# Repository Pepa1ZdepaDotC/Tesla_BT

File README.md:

# Tesla 1128A repair and BT upgrade

[Schematic](https://github.com/Pepa1ZdepaDotC/Tesla_BT/blob/main/Tesla_rev_2/Tesla_sextant_BT.pdf)

[Interactive BOM](https://htmlpreview.github.io/?https://github.com/Pepa1ZdepaDotC/Tesla_a.s._BT/blob/main/BOM/ibom.html)

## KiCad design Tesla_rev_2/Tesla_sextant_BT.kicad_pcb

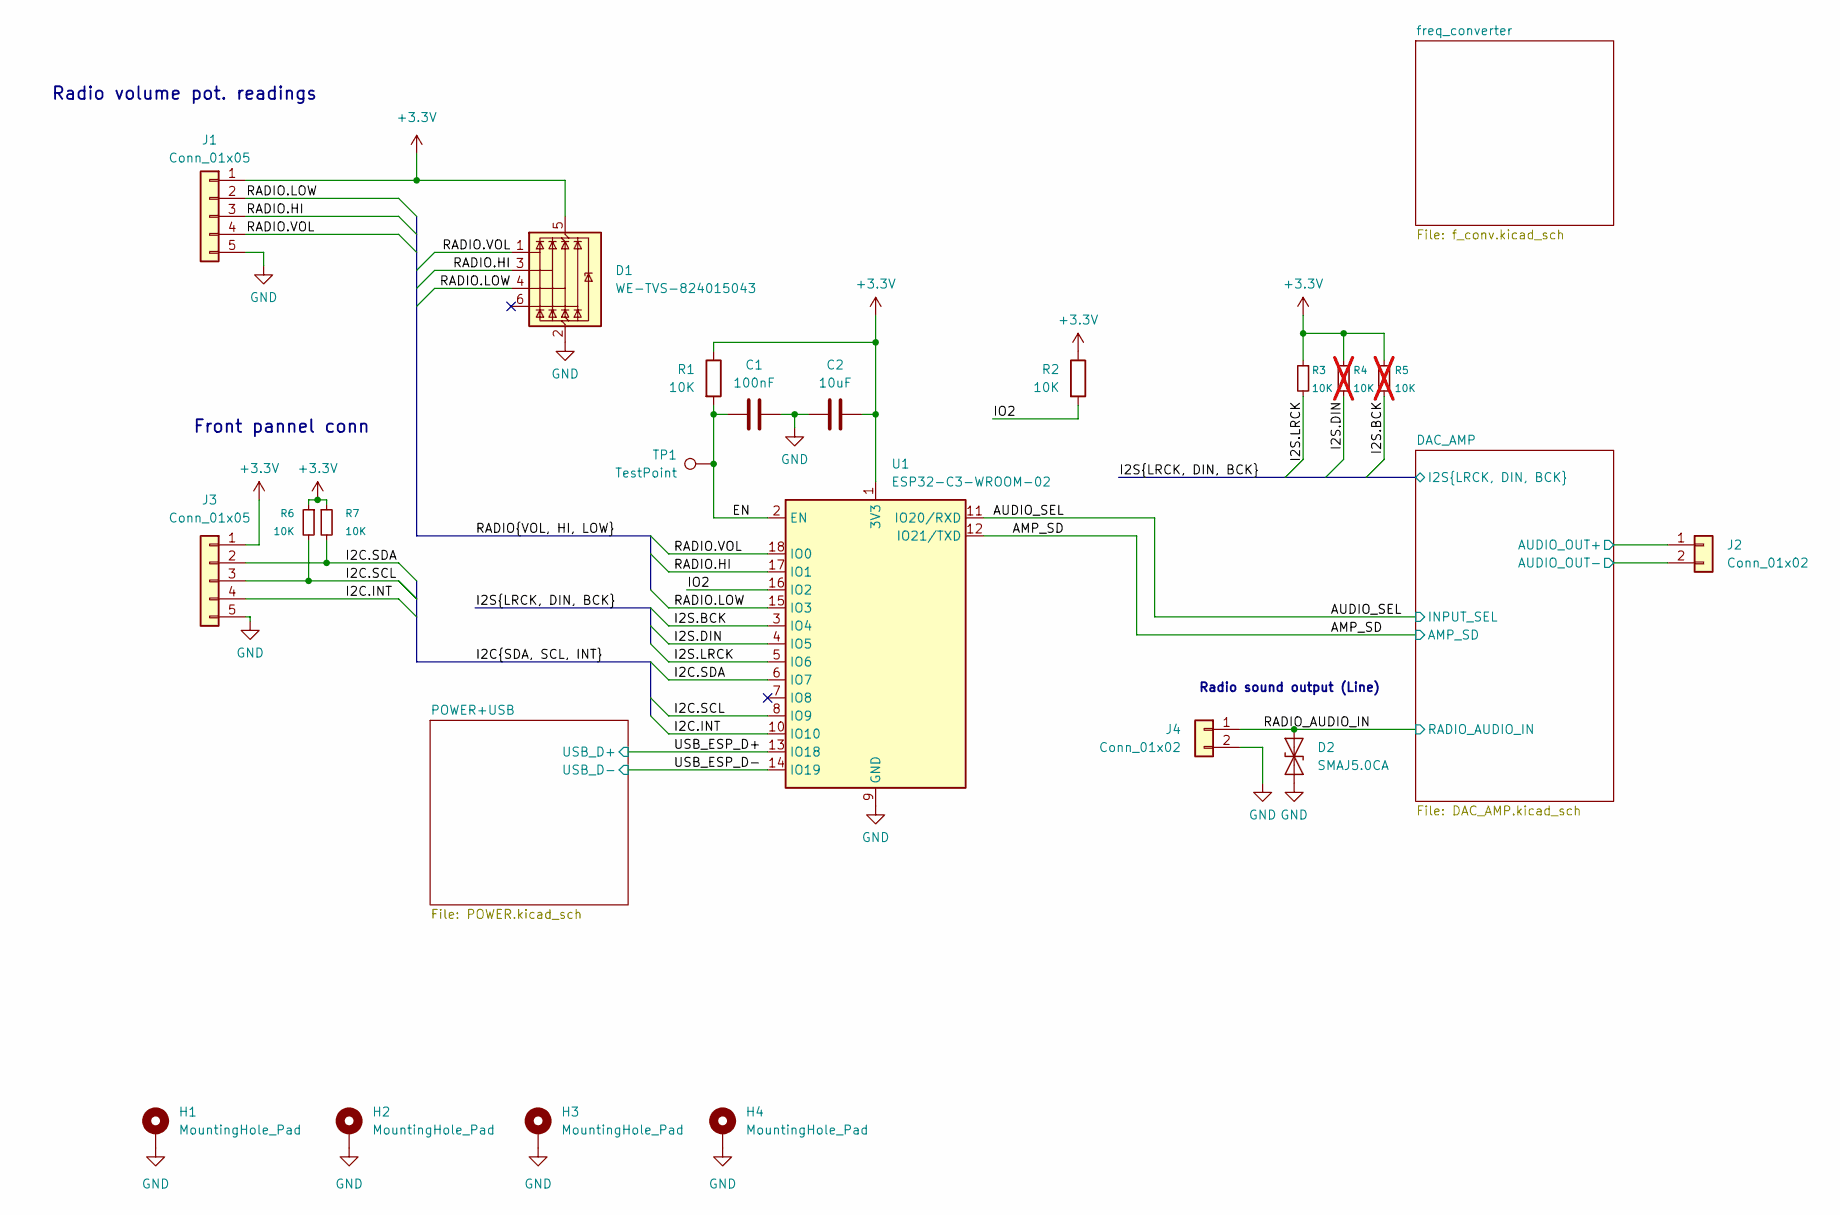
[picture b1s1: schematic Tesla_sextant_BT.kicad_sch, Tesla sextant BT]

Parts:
C1: 100nF; C_0805_2012Metric
C2: 10uF; C_0805_2012Metric
D1: WE-TVS-824015043; SOT-23-6
D2: SMAJ5.0CA; D_SMA
H1, H2, H3, H4: MountingHole_Pad; MountingHole_4.3mm_M4_DIN965_Pad_TopBottom
J1, J3: Conn_01x05; PinSocket_1x05_P2.00mm_Vertical
J2, J4: Conn_01x02; Conn_Solder_1x02_SMD
R1, R2, R3, R6, R7: 10K; R_0805_2012Metric
R4, R5: 10K; R_0805_2012Metric; not fitted
TP1: TestPoint; TestPoint_Pad_D2.5mm
U1: ESP32-C3-WROOM-02

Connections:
+3.3V: C2.1, D1.5 (VBUS), J1.1, J3.1, R1.1, R2.1, R3.1, R4.1, R5.1, R6.1, R7.1, U1.1 (3V3); also elsewhere on the board
/AMP_SD: U1.12 (IO21/TXD); also elsewhere on the board
/AUDIO_SEL: U1.11 (IO20/RXD); also elsewhere on the board
/DAC_AMP/AUDIO_OUT+: J2.1; also elsewhere on the board
/DAC_AMP/AUDIO_OUT-: J2.2; also elsewhere on the board
/EN: C1.2, R1.2, TP1.1, U1.2 (EN)
/I2C.INT: J3.4, U1.10 (IO10)
/I2C.SCL: J3.3, R6.2, U1.8 (IO9)
/I2C.SDA: J3.2, R7.2, U1.6 (IO7)
/I2S.BCK: R5.2, U1.3 (IO4); also elsewhere on the board
/I2S.DIN: R4.2, U1.4 (IO5); also elsewhere on the board
/I2S.LRCK: R3.2, U1.5 (IO6); also elsewhere on the board
/IO2: R2.2, U1.16 (IO2)
/RADIO.HI: D1.3 (I/O2), J1.3, U1.17 (IO1)
/RADIO.LOW: D1.4 (I/O3), J1.2, U1.15 (IO3)
/RADIO.VOL: D1.1 (I/O1), J1.4, U1.18 (IO0)
/RADIO_AUDIO_IN: D2.1 (A1), J4.1; also elsewhere on the board
/USB_ESP_D+: U1.13 (IO18); also elsewhere on the board
/USB_ESP_D-: U1.14 (IO19); also elsewhere on the board
GND: C1.1, C2.2, D1.2 (GND), D2.2 (A2), H1.1, H2.1, H3.1, H4.1, J1.5, J3.5, J4.2, U1.9 (GND), U1.19 (GND); also elsewhere on the board

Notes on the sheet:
Radio volume pot. readings
Radio sound output (Line)
Front pannel conn

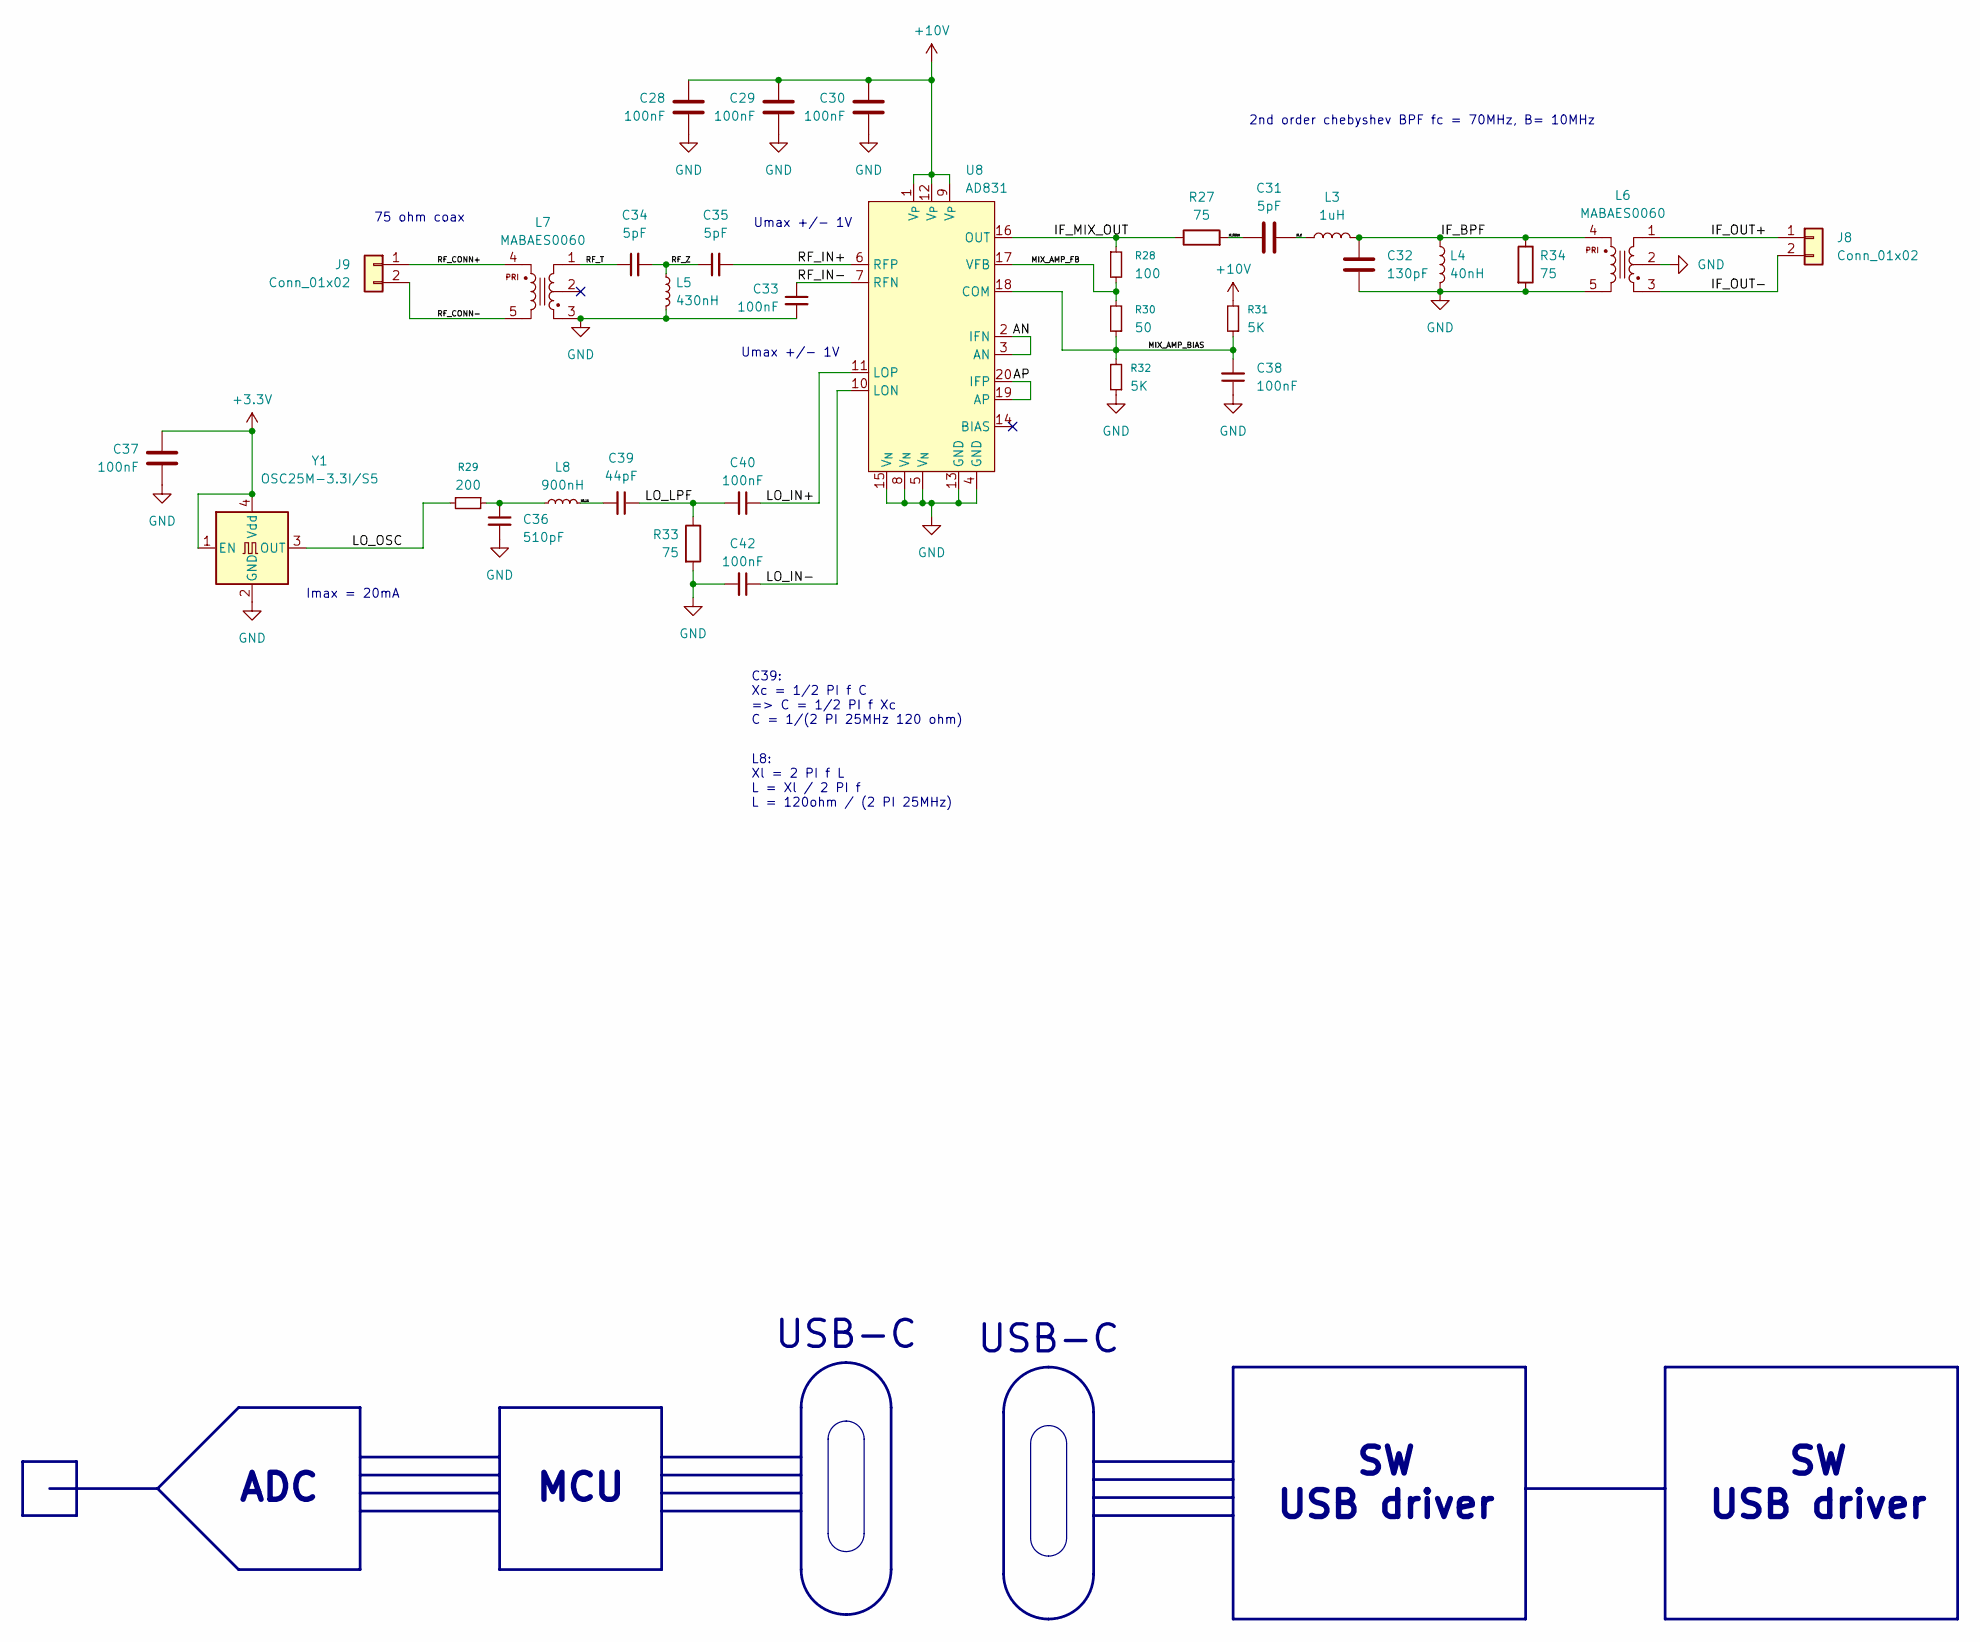
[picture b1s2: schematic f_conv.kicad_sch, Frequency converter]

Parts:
C28, C29, C30, C37, C38: 100nF; C_0805_2012Metric
C31, C34, C35: 5pF; C_0603_1608Metric
C32: 130pF; C_0603_1608Metric
C33, C40, C42: 100nF; C_0603_1608Metric
C36: 510pF; C_0603_1608Metric
C39: 44pF; C_0603_1608Metric
J8, J9: Conn_01x02; Conn_Solder_1x02_SMD
L3: 1uH; L_0603_1608Metric
L4: 40nH; L_0603_1608Metric
L5: 430nH; L_0603_1608Metric
L6, L7: MABAES0060; SM-22
L8: 900nH; L_0603_1608Metric
R27, R33, R34: 75; R_0805_2012Metric
R28: 100; R_0805_2012Metric
R29: 200; R_0805_2012Metric
R30: 50; R_0805_2012Metric
R31, R32: 5K; R_0805_2012Metric
U8: AD831; PLCC-20
Y1: OSC25M-3.3I/S5; Oscillator_SMD_Fordahl_DFAS15-4Pin_5.0x3.2mm_HandSoldering

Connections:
+3.3V: C37.2, Y1.1 (EN), Y1.4 (Vdd); also elsewhere on the board
+10V: C28.2, C29.2, C30.2, R31.2, U8.1 (V_{P}), U8.9 (V_{P}), U8.12 (V_{P}); also elsewhere on the board
/freq_converter/AN: U8.2 (IFN), U8.3 (AN)
/freq_converter/AP: U8.19 (AP), U8.20 (IFP)
/freq_converter/IF_BPF: C32.2, L3.2, L4.1, L6.4, R34.1
/freq_converter/IF_C: C31.2, L3.1
/freq_converter/IF_MIX_OUT: R27.1, R28.1, U8.16 (OUT)
/freq_converter/IF_OUT+: J8.1, L6.1
/freq_converter/IF_OUT-: J8.2, L6.3
/freq_converter/IF_TERM: C31.1, R27.2
/freq_converter/LO_IN+: C40.1, U8.11 (LOP)
/freq_converter/LO_IN-: C42.1, U8.10 (LON)
/freq_converter/LO_L1: C39.2, L8.2
/freq_converter/LO_LPF: C39.1, C40.2, R33.1
/freq_converter/LO_OSC: R29.2, Y1.3 (OUT)
/freq_converter/MIX_AMP_BIAS: C38.2, R30.1, R31.1, R32.2, U8.18 (COM)
/freq_converter/MIX_AMP_FB: R28.2, R30.2, U8.17 (VFB)
/freq_converter/RF_CONN+: J9.1, L7.4
/freq_converter/RF_CONN-: J9.2, L7.5
/freq_converter/RF_IN+: C35.2, U8.6 (RFP)
/freq_converter/RF_IN-: C33.1, U8.7 (RFN)
/freq_converter/RF_T: C34.1, L7.1
/freq_converter/RF_Z: C34.2, C35.1, L5.1
GND: C28.1, C29.1, C30.1, C32.1, C33.2, C36.2, C37.1, C38.1, C42.2, L4.2, L5.2, L6.2, L6.5, L7.3, R32.1, R33.2, R34.2, U8.4 (GND), U8.5 (V_{N}), U8.8 (V_{N}), U8.13 (GND), U8.15 (V_{N}), Y1.2 (GND); also elsewhere on the board
unnamed: C36.1, L8.1, R29.1

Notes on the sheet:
L8: Xl = 2 PI f L L = Xl / 2 PI f L = 120ohm / (2 PI 25MHz)
2nd order chebyshev BPF fc = 70MHz, B= 10MHz
Umax +/- 1V
SW USB driver
ADC
C39: Xc = 1/2 PI f C => C = 1/2 PI f Xc C = 1/(2 PI 25MHz 120 ohm)
Imax = 20mA
USB-C
75 ohm coax
MCU

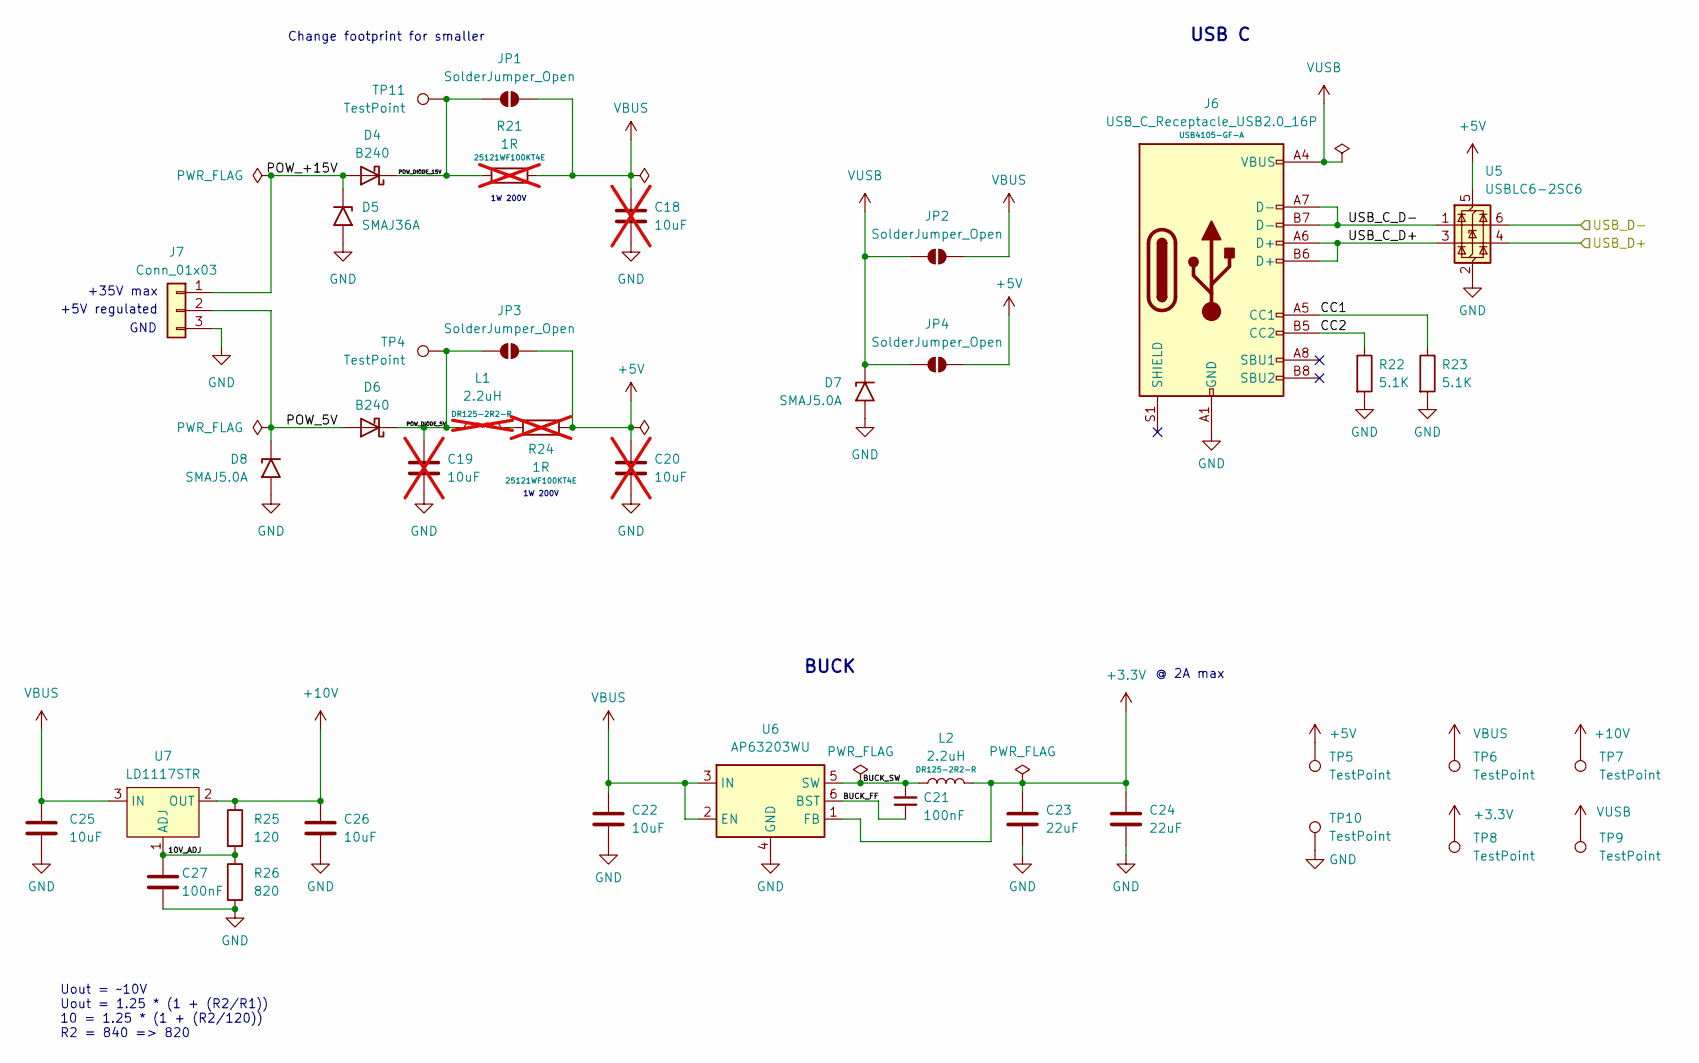
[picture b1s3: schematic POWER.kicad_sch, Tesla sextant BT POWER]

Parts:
C18, C19, C20: 10uF; C_0805_2012Metric; not fitted
C21, C27: 100nF; C_0805_2012Metric
C22, C25, C26: 10uF; C_0805_2012Metric
C23, C24: 22uF; C_0805_2012Metric
D4, D6: B240; D_SMB
D5: SMAJ36A; D_SMA
D7, D8: SMAJ5.0A; D_SMA
J6: USB_C_Receptacle_USB2.0_16P; USB_C_Receptacle_GCT_USB4105-xx-A_16P_TopMnt_Horizontal; Part_num USB4105-GF-A
J7: Conn_01x03; Conn_Solder_1x03_SMD
JP1, JP2, JP3, JP4: SolderJumper_Open; SolderJumper-2_P1.3mm_Open_TrianglePad1.0x1.5mm
L1: 2.2uH; L_12x12mm_H8mm; Part_num DR125-2R2-R; not fitted
L2: 2.2uH; L_12x12mm_H8mm; Part_num DR125-2R2-R
R21, R24: 1R; R_2512_6332Metric; Part_num 25121WF100KT4E; not fitted
R22, R23: 5.1K; R_0805_2012Metric
R25: 120; R_0805_2012Metric
R26: 820; R_0805_2012Metric
TP4, TP5, TP6, TP7, TP8, TP9, TP10, TP11: TestPoint; TestPoint_Pad_D2.5mm
U5: USBLC6-2SC6; SOT-23-6
U6: AP63203WU; TSOT-23-6
U7: LD1117STR; SOT-223

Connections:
+3.3V: C23.1, C24.1, L2.2, TP8.1, U6.1 (FB); also elsewhere on the board
+5V: C20.1, JP3.2 (B), JP4.2 (B), R24.1, TP5.1, U5.5 (VBUS); also elsewhere on the board
+10V: C26.1, R25.1, TP7.1, U7.2 (OUT), U7.4 (OUT); also elsewhere on the board
/POWER+USB/10V_ADJ: C27.1, R25.2, R26.1, U7.1 (ADJ)
/POWER+USB/BUCK_FF: C21.1, U6.6 (BST)
/POWER+USB/BUCK_SW: C21.2, L2.1, U6.5 (SW)
/POWER+USB/CC1: J6.A5 (CC1), R23.1
/POWER+USB/CC2: J6.B5 (CC2), R22.1
/POWER+USB/POW_5V: D6.2 (A), D8.1 (A1), J7.2
/POWER+USB/POW_+15V: D4.2 (A), D5.1 (A1), J7.1
/POWER+USB/POW_DIODE_5V: C19.1, D6.1 (K), JP3.1 (A), L1.1, TP4.1
/POWER+USB/POW_DIODE_15V: D4.1 (K), JP1.1 (A), R21.2, TP11.1
/POWER+USB/USB_C_D+: J6.A6 (D+), J6.B6 (D+), U5.3 (I/O2)
/POWER+USB/USB_C_D-: J6.A7 (D-), J6.B7 (D-), U5.1 (I/O1)
/USB_ESP_D+: U5.4 (I/O2); also elsewhere on the board
/USB_ESP_D-: U5.6 (I/O1); also elsewhere on the board
GND: C18.2, C19.2, C20.2, C22.2, C23.2, C24.2, C25.2, C26.2, C27.2, D5.2 (A2), D7.2 (A2), D8.2 (A2), J6.A1 (GND), J6.A12 (GND), J6.B1 (GND), J6.B12 (GND), J7.3, R22.2, R23.2, R26.2, TP10.1, U5.2 (GND), U6.4 (GND); also elsewhere on the board
unnamed: L1.2, R24.2
VBUS: C18.1, C22.1, C25.1, JP1.2 (B), JP2.2 (B), R21.1, TP6.1, U6.2 (EN), U6.3 (IN), U7.3 (IN)
VUSB: D7.1 (A1), J6.A4 (VBUS), J6.A9 (VBUS), J6.B4 (VBUS), J6.B9 (VBUS), JP2.1 (A), JP4.1 (A), TP9.1

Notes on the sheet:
Uout = ~10V Uout = 1.25 * (1 + (R2/R1)) 10 = 1.25 * (1 + (R2/120)) R2 = 840 => 820
@ 2A max
+5V regulated
GND
1W 200V
+35V max
Change footprint for smaller
BUCK
USB C

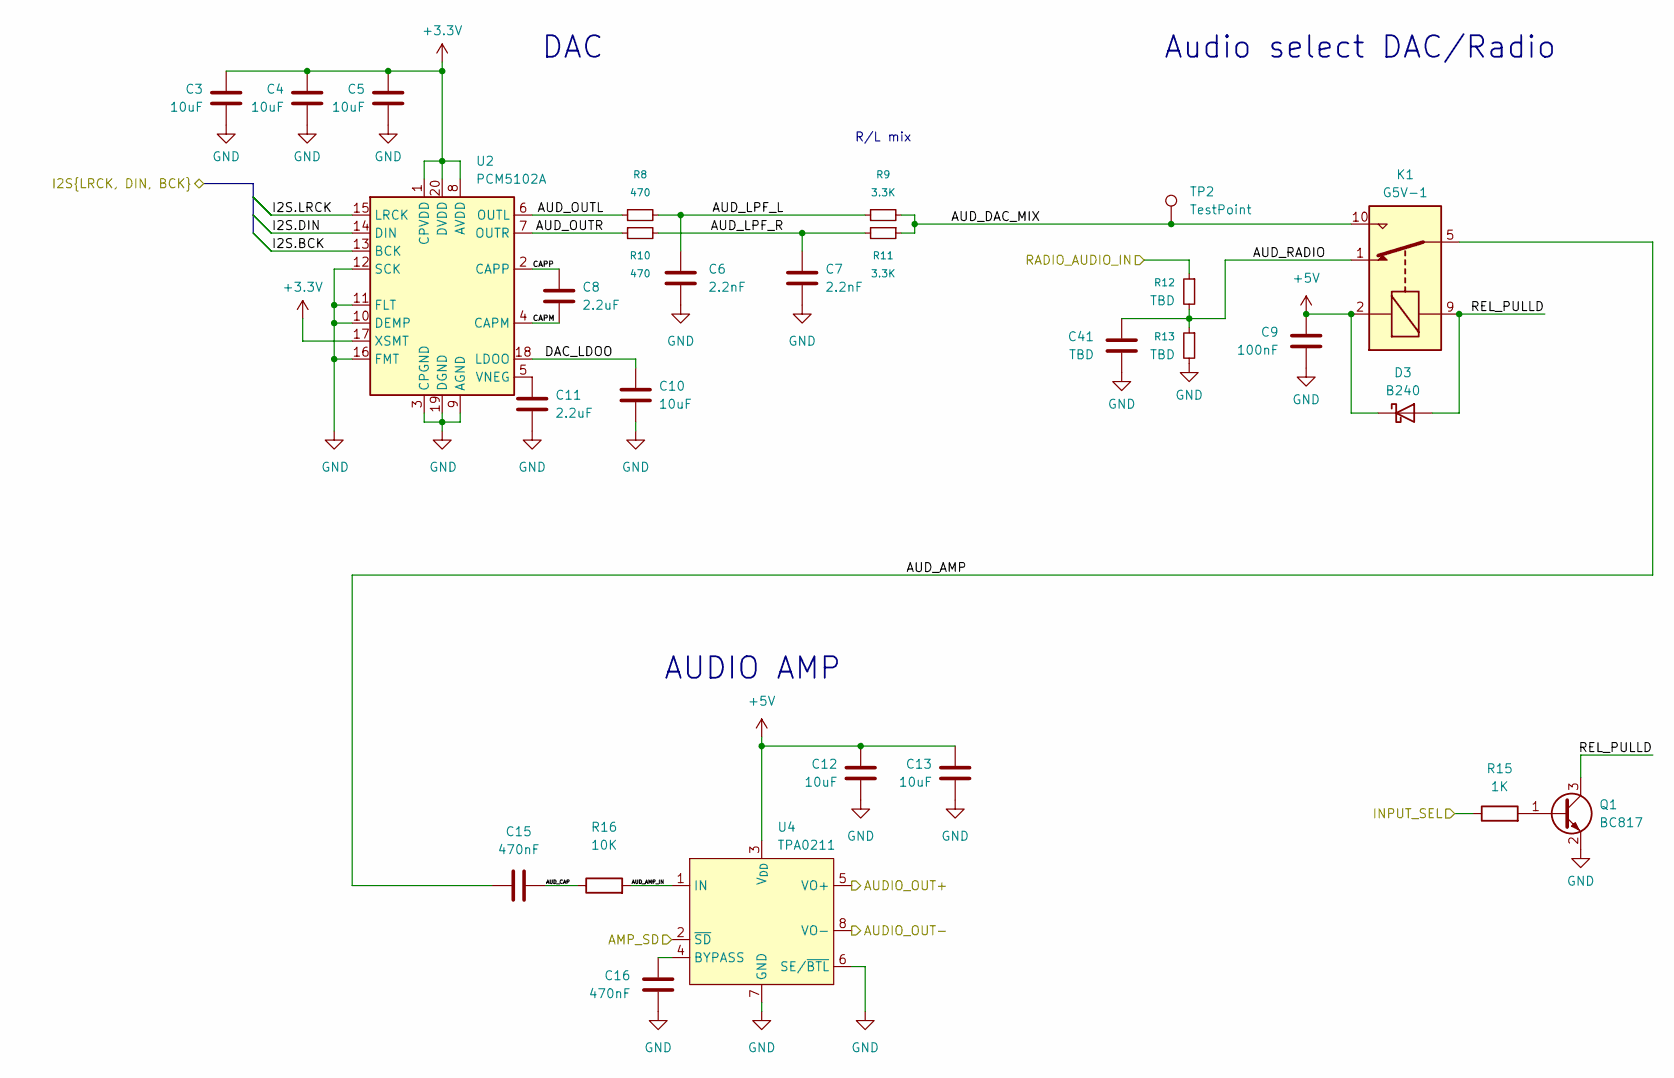
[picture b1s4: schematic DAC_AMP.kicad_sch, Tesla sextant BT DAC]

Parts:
C3, C4, C5, C10, C12, C13: 10uF; C_0805_2012Metric
C6, C7: 2.2nF; C_0805_2012Metric
C8, C11: 2.2uF; C_0805_2012Metric
C9: 100nF; C_0805_2012Metric
C15, C16: 470nF; C_0805_2012Metric
C41: TBD; C_0805_2012Metric
D3: B240; D_SMB
K1: G5V-1; Relay_SPDT_Omron_G5V-1
Q1: BC817; SOT-23
R8, R10: 470; R_0805_2012Metric
R9, R11: 3.3K; R_0805_2012Metric
R12, R13: TBD; R_0805_2012Metric
R15: 1K; R_0805_2012Metric
R16: 10K; R_0805_2012Metric
TP2: TestPoint; TestPoint_Pad_D2.5mm
U2: PCM5102A; TSSOP-20_4.4x6.5mm_P0.65mm
U4: TPA0211; HVSSOP-8-1EP_3x3mm_P0.65mm_EP1.57x1.89mm_ThermalVias

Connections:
+3.3V: C3.1, C4.1, C5.1, U2.1 (CPVDD), U2.8 (AVDD), U2.17 (XSMT), U2.20 (DVDD); also elsewhere on the board
+5V: C9.1, C12.1, C13.1, D3.1 (K), K1.2, U4.3 (V_{DD}); also elsewhere on the board
/AMP_SD: U4.2 (~SD); also elsewhere on the board
/AUDIO_SEL: R15.1; also elsewhere on the board
/DAC_AMP/AUDIO_OUT+: U4.5 (VO+); also elsewhere on the board
/DAC_AMP/AUDIO_OUT-: U4.8 (VO-); also elsewhere on the board
/DAC_AMP/AUD_AMP: C15.1, K1.5, K1.6
/DAC_AMP/AUD_AMP_IN: R16.2, U4.1 (IN)
/DAC_AMP/AUD_CAP: C15.2, R16.1
/DAC_AMP/AUD_DAC_MIX: K1.10, R9.2, R11.1, TP2.1
/DAC_AMP/AUD_LPF_L: C6.1, R8.2, R9.1
/DAC_AMP/AUD_LPF_R: C7.1, R10.2, R11.2
/DAC_AMP/AUD_OUTL: R8.1, U2.6 (OUTL)
/DAC_AMP/AUD_OUTR: R10.1, U2.7 (OUTR)
/DAC_AMP/AUD_RADIO: C41.1, K1.1, R12.2, R13.1
/DAC_AMP/CAPM: C8.2, U2.4 (CAPM)
/DAC_AMP/CAPP: C8.1, U2.2 (CAPP)
/DAC_AMP/DAC_LDOO: C10.1, U2.18 (LDOO)
/DAC_AMP/REL_PULLD: D3.2 (A), K1.9, Q1.3 (C)
/I2S.BCK: U2.13 (BCK); also elsewhere on the board
/I2S.DIN: U2.14 (DIN); also elsewhere on the board
/I2S.LRCK: U2.15 (LRCK); also elsewhere on the board
/RADIO_AUDIO_IN: R12.1; also elsewhere on the board
GND: C3.2, C4.2, C5.2, C6.2, C7.2, C9.2, C10.2, C11.2, C12.2, C13.2, C16.2, C41.2, Q1.2 (E), R13.2, U2.3 (CPGND), U2.9 (AGND), U2.10 (DEMP), U2.11 (FLT), U2.12 (SCK), U2.16 (FMT), U2.19 (DGND), U4.6 (SE/~BTL), U4.7 (GND); also elsewhere on the board
unnamed: Q1.1 (B), R15.2
unnamed: C11.1, U2.5 (VNEG)
unnamed: C16.1, U4.4 (BYPASS)

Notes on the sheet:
Audio select DAC/Radio
AUDIO AMP
R/L mix
DAC

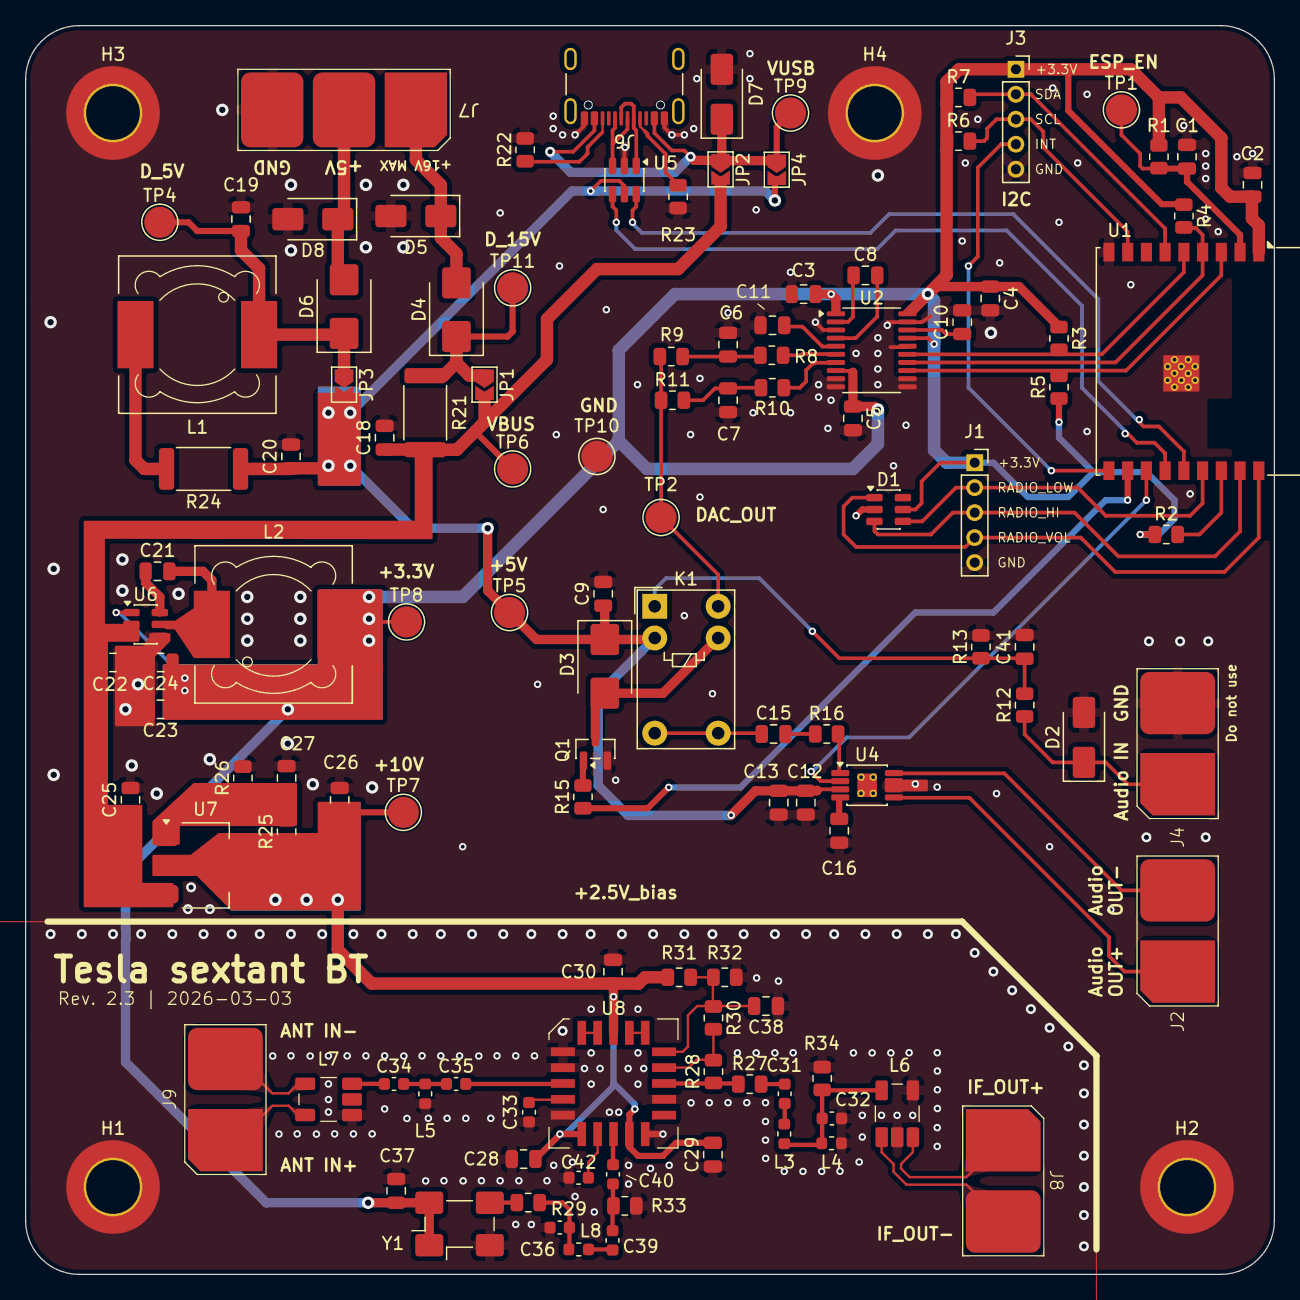
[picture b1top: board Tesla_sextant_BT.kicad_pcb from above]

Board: 4 copper layers, 100.0 x 100.0 mm, 121 parts (0 on the bottom side), 74 nets.

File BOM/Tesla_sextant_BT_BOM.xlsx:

Reference | Value | Footprint | Datasheet | Qty | Part_num | DNP | Exclude from BOM | Needs ordering
C1,C9,C14,C21,C27,C28,C29,C30,C36,C37,C38 | 100nF | Capacitor_SMD:C_0805_2012Metric | ~ | 11 |  |  |  | x
C15,C16 | 470nF | Capacitor_SMD:C_0805_2012Metric | ~ | 2
C18,C19,C20 | 10uF | Capacitor_SMD:C_0805_2012Metric | ~ | 3 |  | DNP | Excluded from BOM | x
C2,C3,C4,C5,C10,C12,C13,C17,C22,C25,C26 | 10uF | Capacitor_SMD:C_0805_2012Metric | ~ | 11 |  |  |  | x
C23,C24 | 22uF | Capacitor_SMD:C_0805_2012Metric | ~ | 2
C31 | 5.6pF | Capacitor_SMD:C_0603_1608Metric | ~ | 1
C32 | 4.7pF | Capacitor_SMD:C_0603_1608Metric | ~ | 1
C33 | 470pF | Capacitor_SMD:C_0603_1608Metric | ~ | 1
C34 | 220pF | Capacitor_SMD:C_0603_1608Metric | ~ | 1
C35 | TBD | Capacitor_SMD:C_0805_2012Metric | ~ | 1 |  |  |  | x
C39,C43 | 2.2nF | Capacitor_SMD:C_0603_1608Metric | ~ | 2
C40,C42 | 100nF | Capacitor_SMD:C_0603_1608Metric | ~ | 2 |  |  |  | x
C41 | TBD | Capacitor_SMD:C_0805_2012Metric | ~ | 1 |  | DNP |  | x
C6,C7 | 2.2nF | Capacitor_SMD:C_0805_2012Metric | ~ | 2 |  |  |  | x
C8,C11 | 2.2uF | Capacitor_SMD:C_0805_2012Metric | ~ | 2
D1 | WE-TVS-824015043 | Package_TO_SOT_SMD:SOT-23-6 | https://www.we-online.com/components/products/datasheet/8240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 | 1
D2 | SMAJ5.0CA | Diode_SMD:D_SMA | https://www.littelfuse.com/media?resourcetype=datasheets&ite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 | 1
D3 | B240 | Diode_SMD:D_SMB | http://www.jameco.com/Jameco/Products/ProdDS/1538777.pdf | 1
D4,D6 | B240 | Diode_SMD:D_SMB | http://www.jameco.com/Jameco/Products/ProdDS/1538777.pdf | 2
D5 | SMAJ36A | Diode_SMD:D_SMA | https://www.littelfuse.com/media?resourcetype=datasheets&ite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 | 1
D7,D8 | SMAJ5.0A | Diode_SMD:D_SMA | https://www.littelfuse.com/media?resourcetype=datasheets&ite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 | 2
H1,H2,H3,H4 | MountingHole_Pad | MountingHole:MountingHole_4.3mm_M4_DIN965_Pad_TopBottom | ~ | 4 |  |  | Excluded from BOM | x
J1,J3 | Conn_01x05 | Connector_PinSocket_2.00mm:PinSocket_1x05_P2.00mm_Vertical | ~ | 2
J2,J4,J8,J9 | Conn_01x02 | Tesla_Library:Conn_Solder_1x02_SMD | ~ | 4 |  |  | Excluded from BOM | x
J6 | USB_C_Receptacle_USB2.0_16P | Connector_USB:USB_C_Receptacle_GCT_USB4105-xx-A_16P_TopMnt_Horizontal | https://www.usb.org/sites/default/files/documents/usb_type-c.zip | 1 | USB4105-GF-A
J7 | Conn_01x03 | Tesla_Library:Conn_Solder_1x03_SMD | ~ | 1 |  |  | Excluded from BOM | x
JP1,JP2,JP3,JP4 | SolderJumper_Open | Jumper:SolderJumper-2_P1.3mm_Open_TrianglePad1.0x1.5mm | ~ | 4 |  |  | Excluded from BOM | x
K1 | G6EU | Relay_THT:Relay_SPDT_Omron_G6E | https://www.omron.com/ecb/products/pdf/en-g6e.pdf | 1
L1 | 2.2uH | Inductor_SMD:L_12x12mm_H8mm | https://www.eaton.com/content/dam/eaton/products/electronic-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 | 1 | DR125-2R2-R | DNP | Excluded from BOM
L2 | 2.2uH | Inductor_SMD:L_12x12mm_H8mm | https://www.eaton.com/content/dam/eaton/products/electronic-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 | 1 | DR125-2R2-R
L3 | 870nF | Inductor_SMD:L_0805_2012Metric | https://www.tme.eu/Document/0d0d46393a0d692394fde600dc165772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 | 1 |  |  |  |  | https://cz.mouser.com/ProductDetail/TDK/MLF2012DR82KT000?qs=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
L4 | 1.3uF | Inductor_SMD:L_0805_2012Metric | ~ | 1 |  |  |  |  | https://cz.mouser.com/ProductDetail/TDK/MLF2012A1R2J?qs=Ydpp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
L5 | TBD | Inductor_SMD:L_0603_1608Metric | ~ | 1
L6 | 12nH | Inductor_SMD:L_0603_1608Metric | ~ | 1 | LQG18HN12NJ00D
L7 | 20nH | Inductor_SMD:L_0603_1608Metric | ~ | 1
L8 | 18nH | Inductor_SMD:L_0603_1608Metric | ~ | 1
Q1 | BC817 | Package_TO_SOT_SMD:SOT-23 | https://www.onsemi.com/pub/Collateral/BC818-D.pdf | 1 |  |  |  | x
R1,R2,R3,R6,R7,R16 | 10K | Capacitor_SMD:C_0805_2012Metric | ~ | 6 |  |  |  | x
R12,R13 | TBD | Resistor_SMD:R_0805_2012Metric | ~ | 2
R14 | 7.5K | Capacitor_SMD:C_0805_2012Metric | ~ | 1 |  |  |  | x
R15,R17 | 1K | Capacitor_SMD:C_0805_2012Metric | ~ | 2 |  |  |  | x
R18 | TBD | Capacitor_SMD:C_0805_2012Metric | ~ | 1 |  | DNP | Excluded from BOM
R19,R20 | 100K | Capacitor_SMD:C_0805_2012Metric | ~ | 2 |  |  |  | x
R21,R24 | 1R | Resistor_SMD:R_2512_6332Metric | https://www.tme.eu/Document/4f50d320a6ddacb273098f84373b6259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 | 2 | 25121WF100KT4E | DNP | Excluded from BOM | x
R22,R23 | 5.1K | Capacitor_SMD:C_0805_2012Metric | ~ | 2 |  |  |  | x
R25 | 120 | Capacitor_SMD:C_0805_2012Metric | ~ | 1
R26 | 820 | Capacitor_SMD:C_0805_2012Metric | ~ | 1
R27,R29,R30,R33 | 50 | Capacitor_SMD:C_0805_2012Metric | ~ | 4
R28 | 100 | Capacitor_SMD:C_0805_2012Metric | ~ | 1
R31,R32 | 5K | Capacitor_SMD:C_0805_2012Metric | ~ | 2 |  |  |  | x
R4,R5 | 10K | Capacitor_SMD:C_0805_2012Metric | ~ | 2 |  | DNP | Excluded from BOM | x
R8,R10 | 470 | Capacitor_SMD:C_0805_2012Metric | ~ | 2
R9,R11 | 3.3K | Capacitor_SMD:C_0805_2012Metric | ~ | 2 |  |  |  | x
TP1,TP2,TP3,TP4,TP5,TP6,TP7,TP8,TP9,TP10,TP11 | TestPoint | TestPoint:TestPoint_Pad_D2.5mm | ~ | 11 |  |  | Excluded from BOM
U1 | ESP32-C3-WROOM-02 | RF_Module:ESP32-C3-WROOM-02 | https://www.espressif.com/sites/default/files/documentation/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 | 1
U2 | PCM5102A | Package_SO:TSSOP-20_4.4x6.5mm_P0.65mm | https://www.ti.com/lit/ds/symlink/pcm5102a.pdf | 1 |  |  |  |  | https://cz.mouser.com/ProductDetail/Texas-Instruments/PCM510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
U3 | OPA2342 | Package_SO:SOIC-8_3.9x4.9mm_P1.27mm | https://www.ti.com/lit/gpn/opa2342 | 1
U4 | TPA0211 | Package_SO:HVSSOP-8-1EP_3x3mm_P0.65mm_EP1.57x1.89mm_ThermalVias | https://www.ti.com/lit/gpn/tpa0211 | 1 |  |  |  |  | https://cz.mouser.com/ProductDetail/Texas-Instruments/TPA021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
U5 | USBLC6-2SC6 | Package_TO_SOT_SMD:SOT-23-6 | https://www.st.com/resource/en/datasheet/usblc6-2.pdf | 1
U6 | AP63203WU | Package_TO_SOT_SMD:TSOT-23-6 | https://www.diodes.com/assets/Datasheets/AP63200-AP63201-AP6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 | 1
U7 | LD1117STR | Package_TO_SOT_SMD:SOT-223 |  | 1
U8 | AD831 | Package_LCC:PLCC-20 | https://www.analog.com/en/products/ad831.html?doc=ad831.pdf | 1 |  |  |  |  | https://cz.mouser.com/ProductDetail/Analog-Devices/AD831APZ?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
Y1 | OSC25M-3.3I/S5 | Oscillator:Oscillator_SMD_Fordahl_DFAS15-4Pin_5.0x3.2mm_HandSoldering | https://www.tme.eu/Document/7a0ceeaed569e73bfa5cc28fb0e463dd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 | 1 |  |  |  |  |  |  |  |  |  |  |  |  |  |  |  |  | a
 |  |  |  | 130

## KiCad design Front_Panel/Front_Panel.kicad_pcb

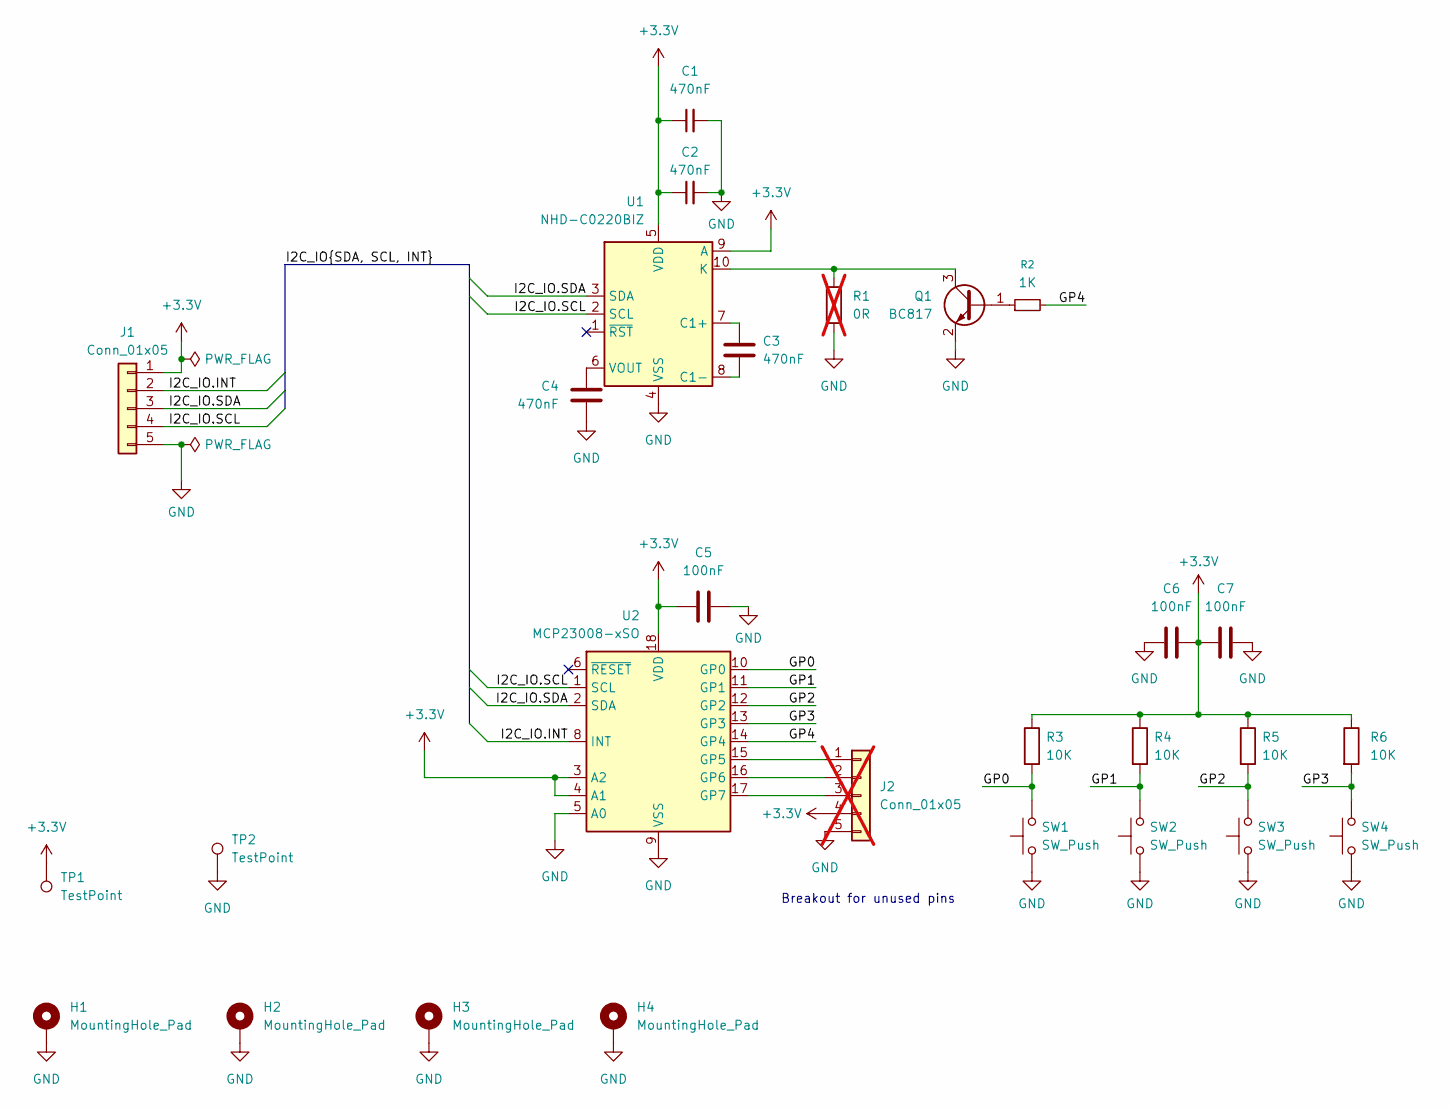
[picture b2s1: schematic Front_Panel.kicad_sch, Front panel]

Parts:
C1, C2, C3, C4: 470nF; C_0805_2012Metric
C5, C6, C7: 100nF; C_0805_2012Metric
H1, H2, H3, H4: MountingHole_Pad; MountingHole_4.3mm_M4_DIN965_Pad_TopBottom
J1: Conn_01x05; PinSocket_1x05_P2.00mm_Vertical
J2: Conn_01x05; PinSocket_1x05_P2.00mm_Vertical; not fitted
Q1: BC817; SOT-23
R1: 0R; R_0805_2012Metric; not fitted
R2: 1K; R_0805_2012Metric
R3, R4, R5, R6: 10K; R_0805_2012Metric
SW1, SW2, SW3, SW4: SW_Push; SW_PUSH-12mm_Wuerth-430476085716
TP1, TP2: TestPoint; TestPoint_Pad_D3.0mm
U1: NHD-C0220BIZ; NHD-C0220BiZ
U2: MCP23008-xSO; SOIC-18W_7.5x11.6mm_P1.27mm

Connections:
+3.3V: C1.1, C2.1, C5.1, C6.2, C7.1, J1.1, J2.4, R3.1, R4.1, R5.1, R6.1, TP1.1, U1.5 (VDD), U1.9 (A), U2.3 (A2), U2.4 (A1), U2.18 (VDD)
/GP0: R3.2, SW1.2, U2.10 (GP0)
/GP1: R4.2, SW2.2, U2.11 (GP1)
/GP2: R5.2, SW3.2, U2.12 (GP2)
/GP3: R6.2, SW4.2, U2.13 (GP3)
/GP4: R2.2, U2.14 (GP4)
/I2C_IO.INT: J1.2, U2.8 (INT)
/I2C_IO.SCL: J1.4, U1.2 (SCL), U2.1 (SCL)
/I2C_IO.SDA: J1.3, U1.3 (SDA), U2.2 (SDA)
GND: C1.2, C2.2, C4.2, C5.2, C6.1, C7.2, H1.1, H2.1, H3.1, H4.1, J1.5, J2.5, Q1.2 (E), R1.2, SW1.1, SW2.1, SW3.1, SW4.1, TP2.1, U1.4 (VSS), U2.5 (A0), U2.9 (VSS)
unnamed: J2.1, U2.15 (GP5)
unnamed: J2.2, U2.16 (GP6)
unnamed: J2.3, U2.17 (GP7)
unnamed: Q1.1 (B), R2.1
unnamed: Q1.3 (C), R1.1, U1.10 (K)
unnamed: C3.1, U1.7 (C1+)
unnamed: C3.2, U1.8 (C1-)
unnamed: C4.1, U1.6 (VOUT)

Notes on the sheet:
Breakout for unused pins
